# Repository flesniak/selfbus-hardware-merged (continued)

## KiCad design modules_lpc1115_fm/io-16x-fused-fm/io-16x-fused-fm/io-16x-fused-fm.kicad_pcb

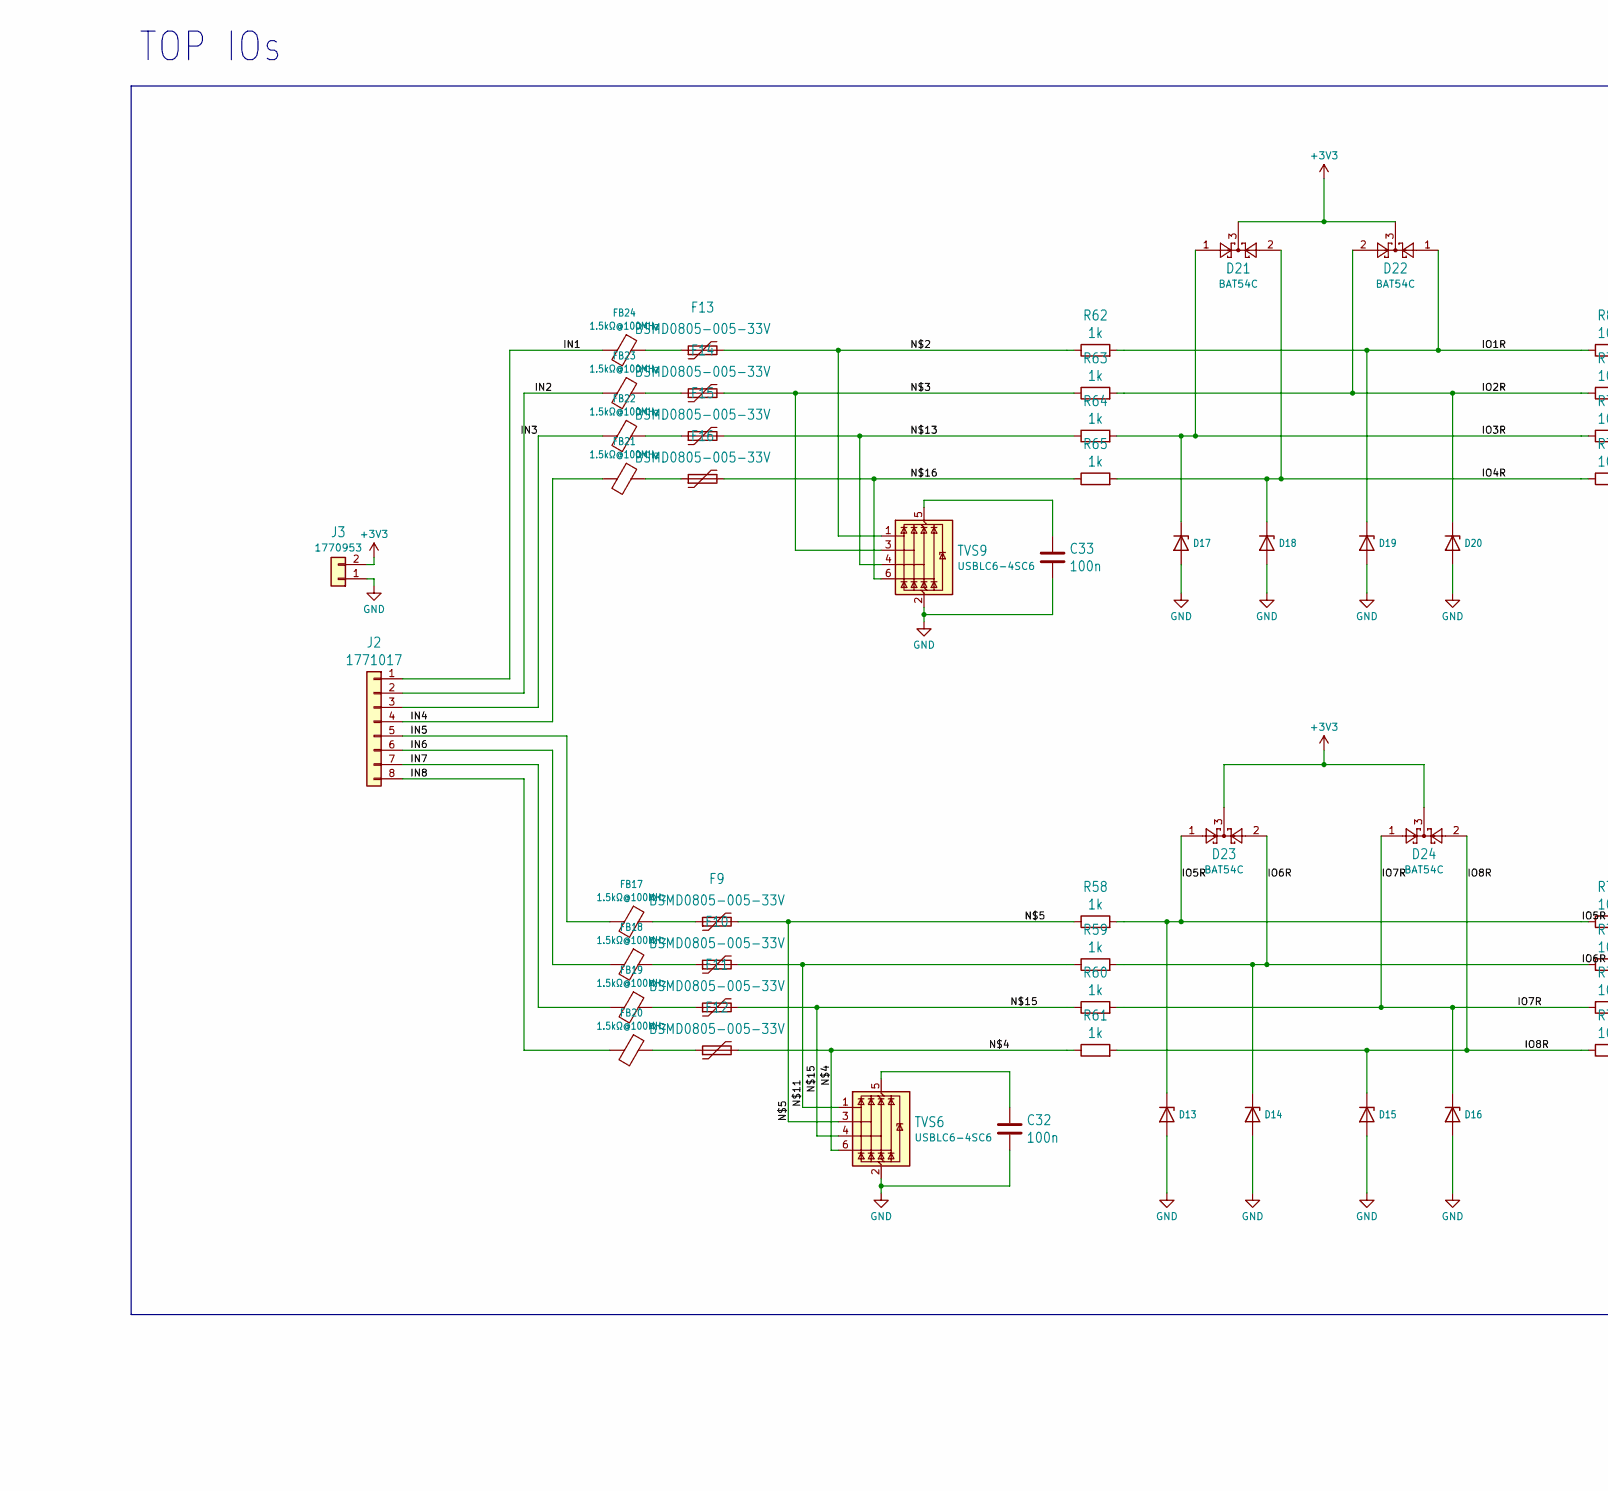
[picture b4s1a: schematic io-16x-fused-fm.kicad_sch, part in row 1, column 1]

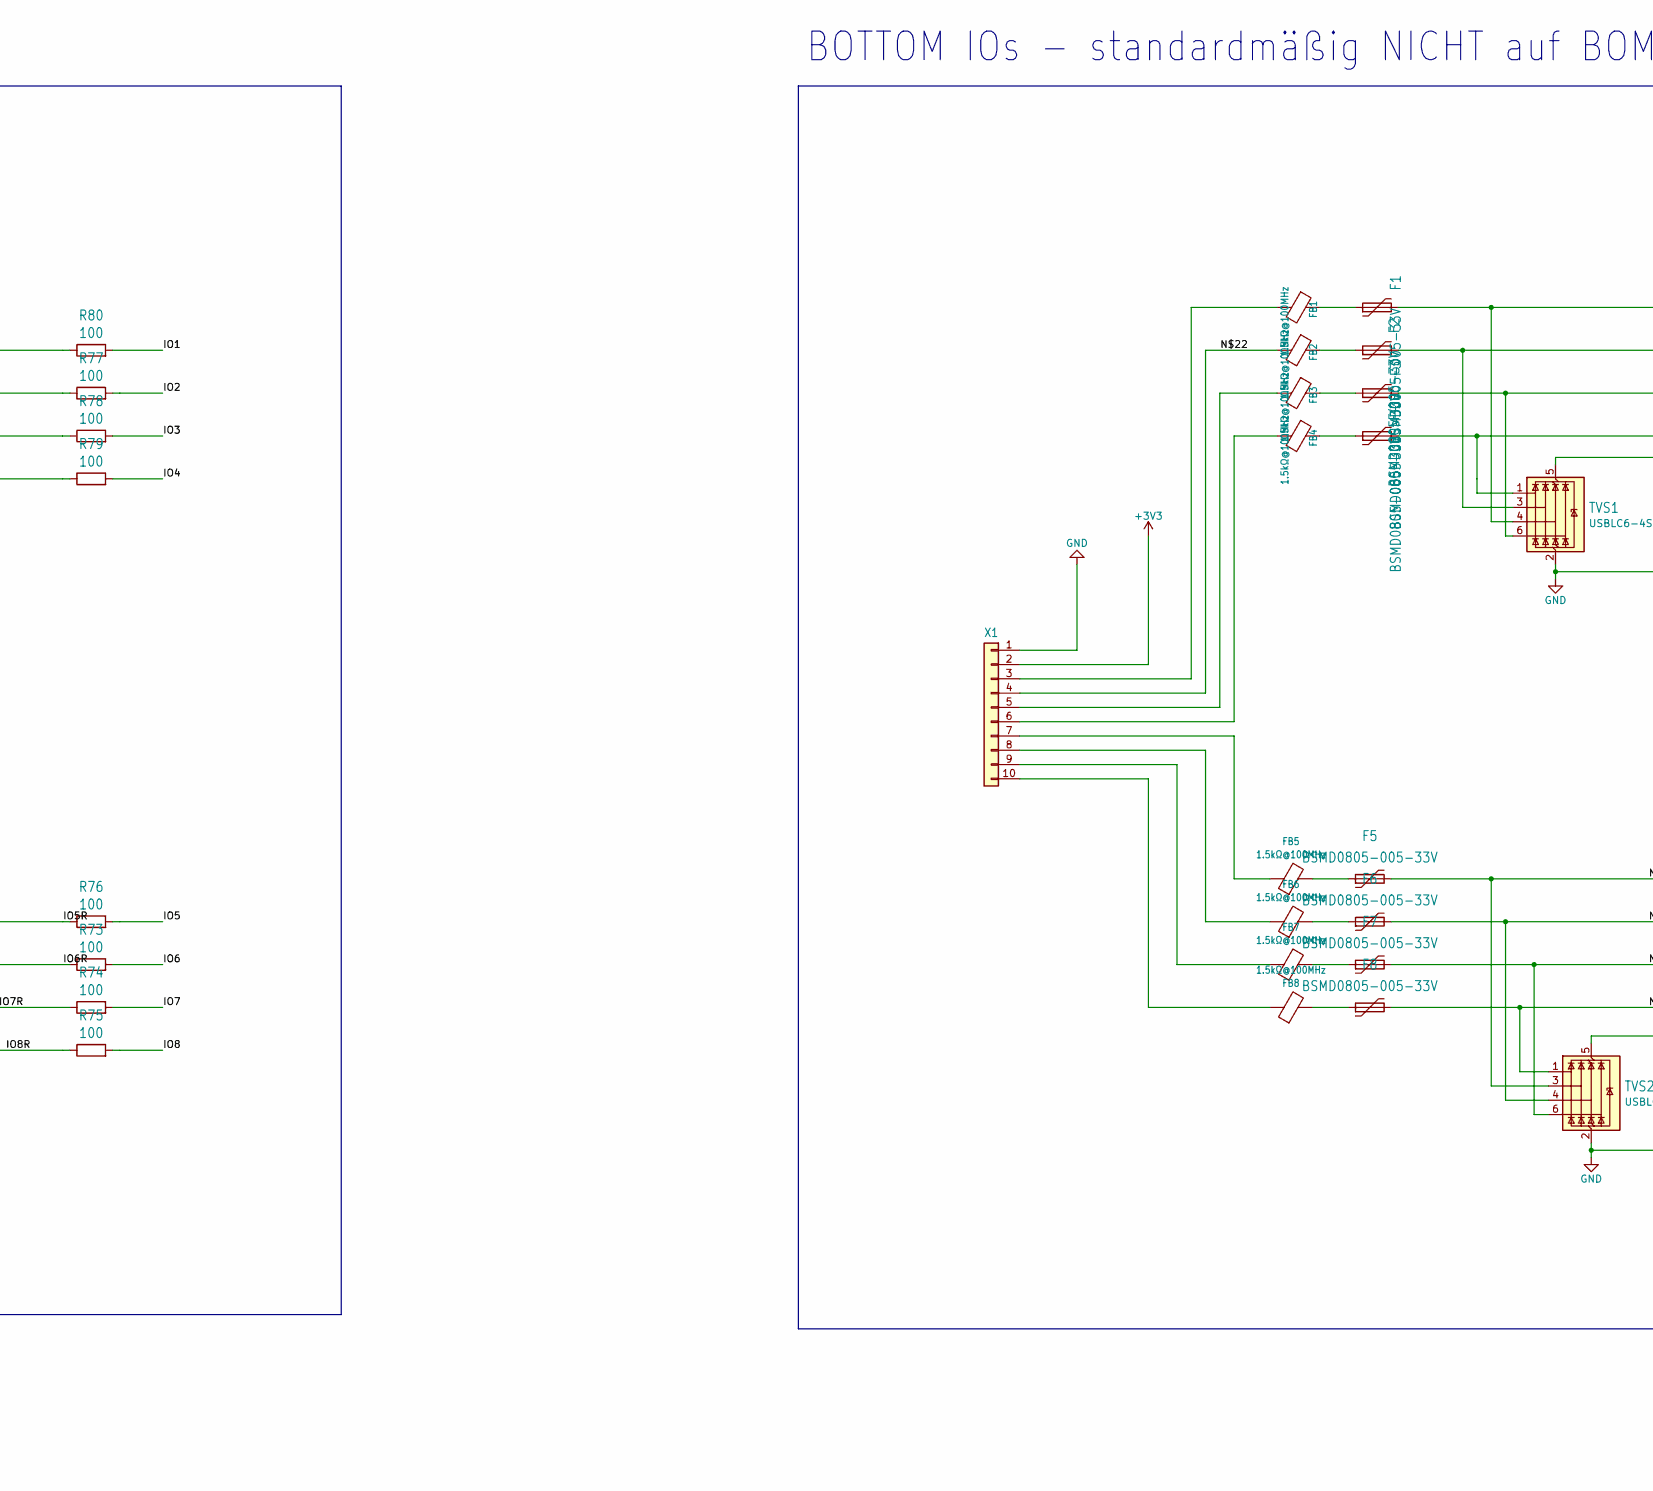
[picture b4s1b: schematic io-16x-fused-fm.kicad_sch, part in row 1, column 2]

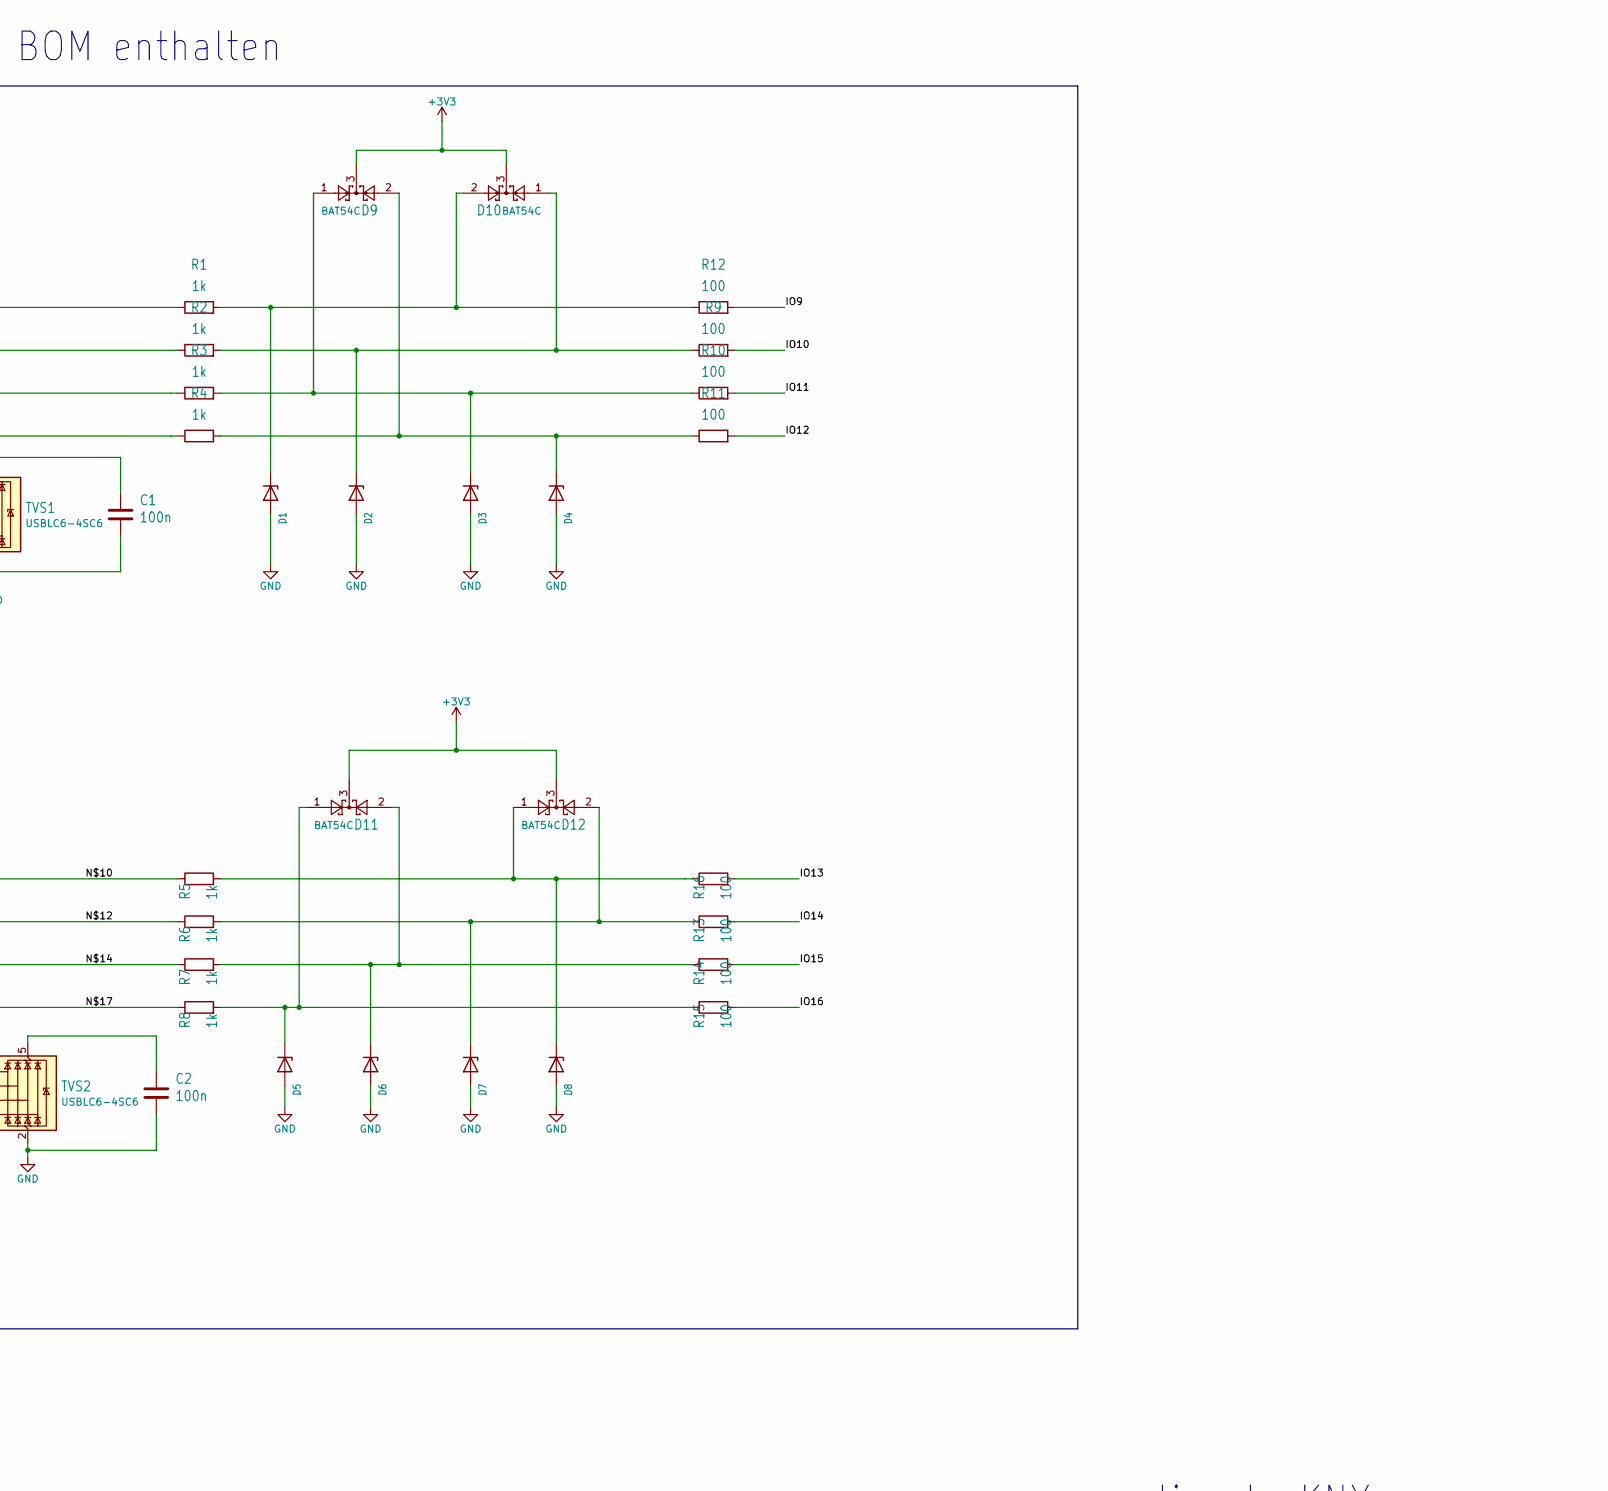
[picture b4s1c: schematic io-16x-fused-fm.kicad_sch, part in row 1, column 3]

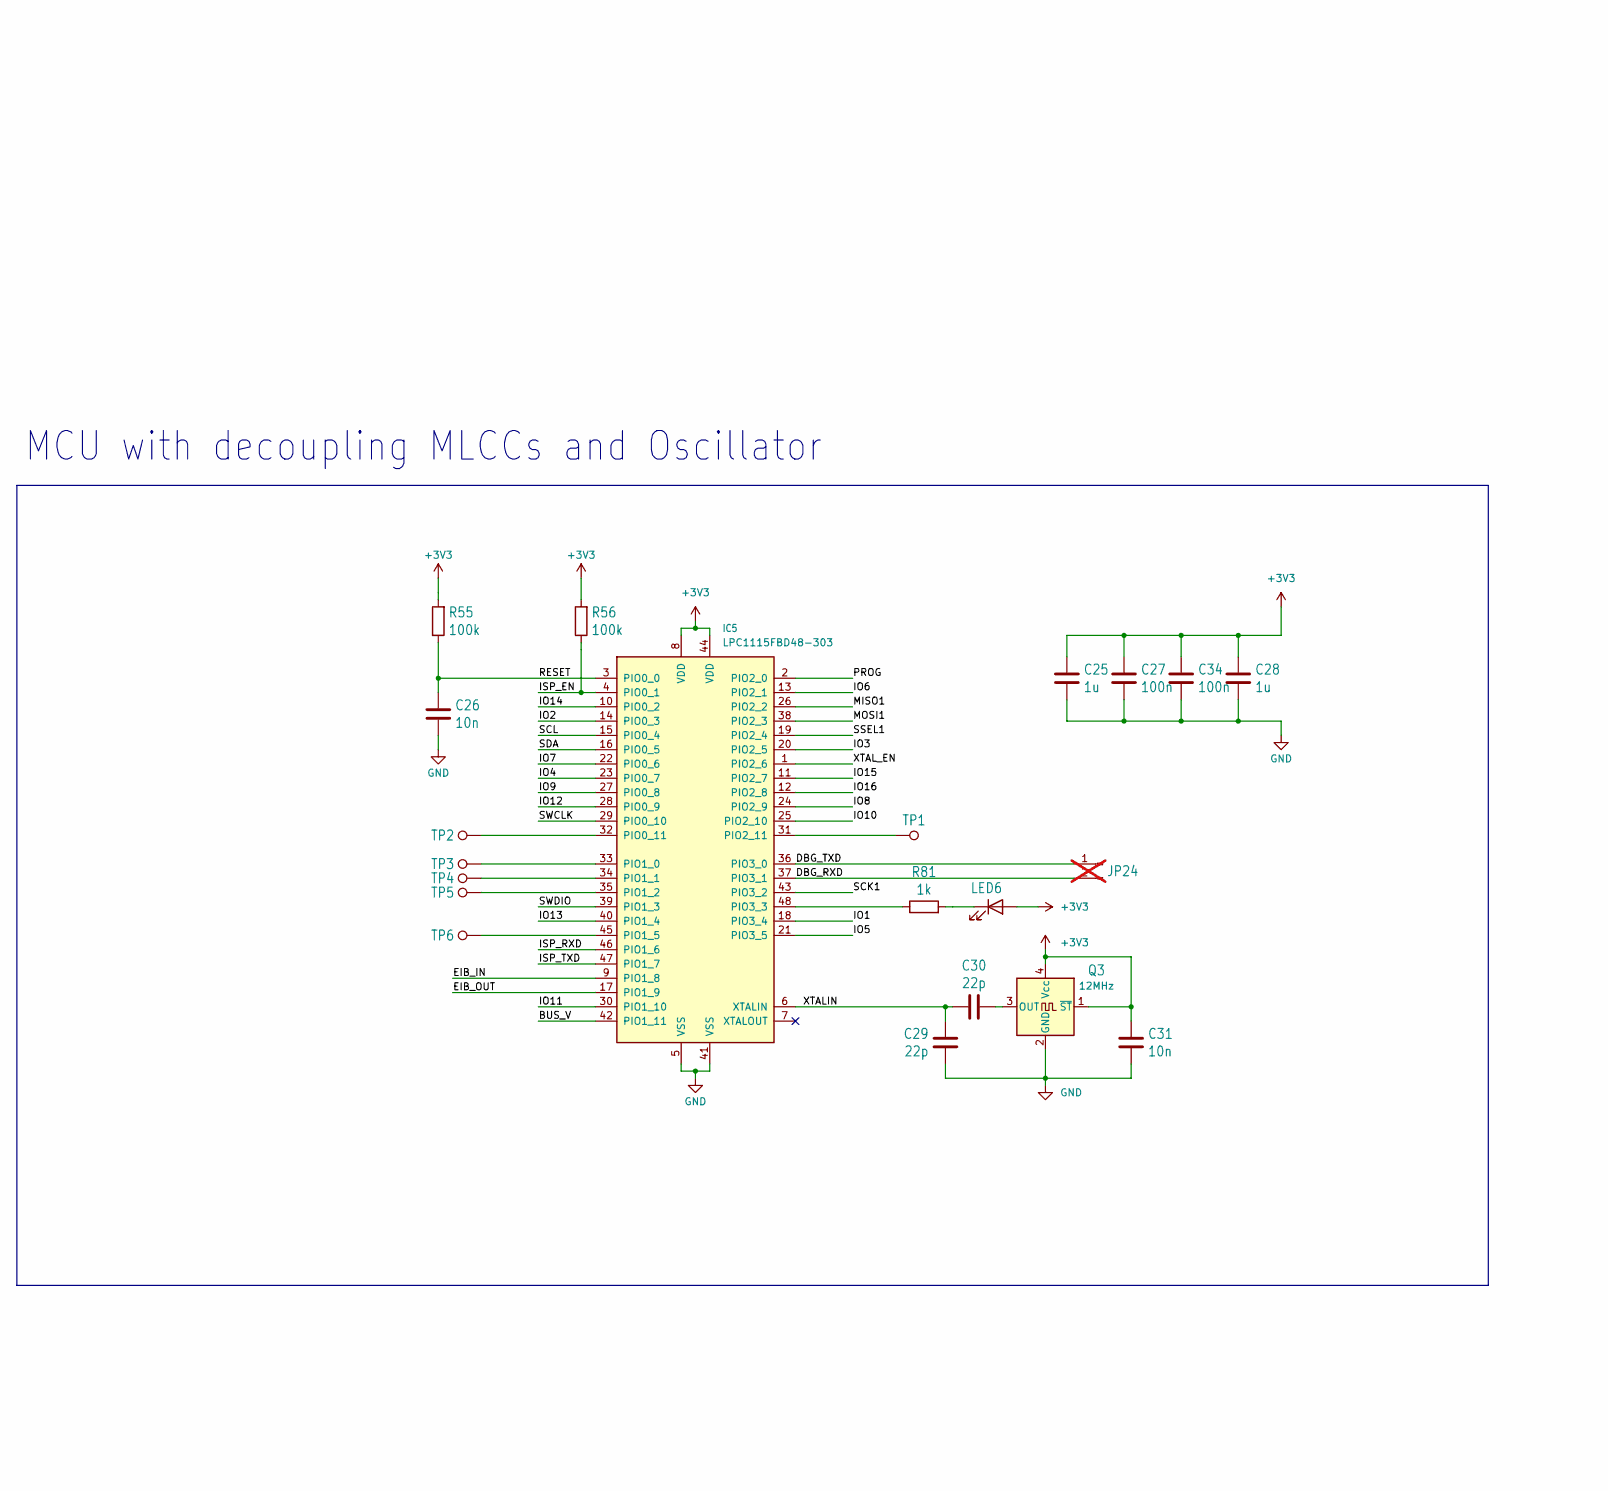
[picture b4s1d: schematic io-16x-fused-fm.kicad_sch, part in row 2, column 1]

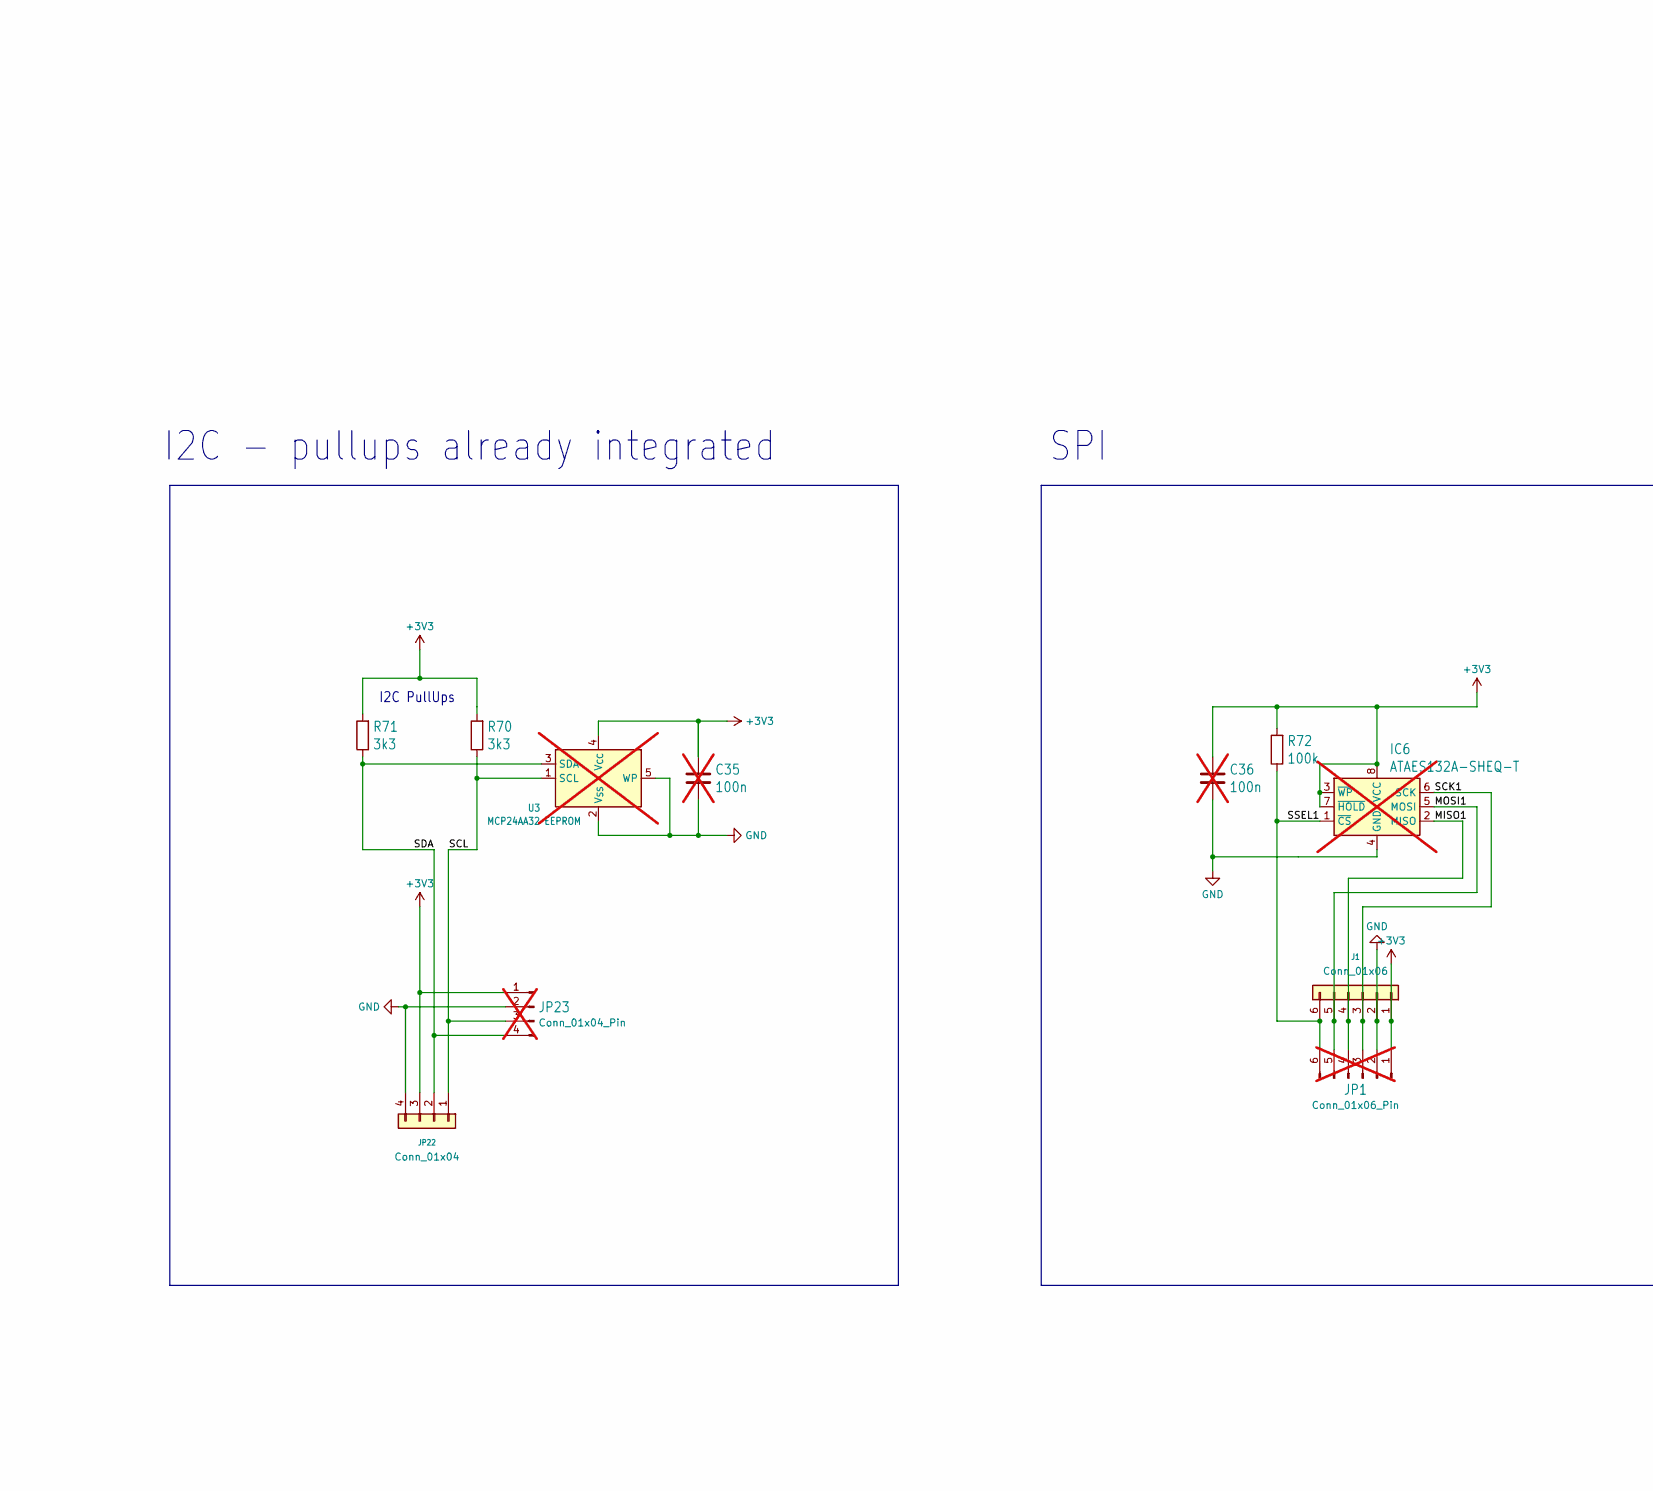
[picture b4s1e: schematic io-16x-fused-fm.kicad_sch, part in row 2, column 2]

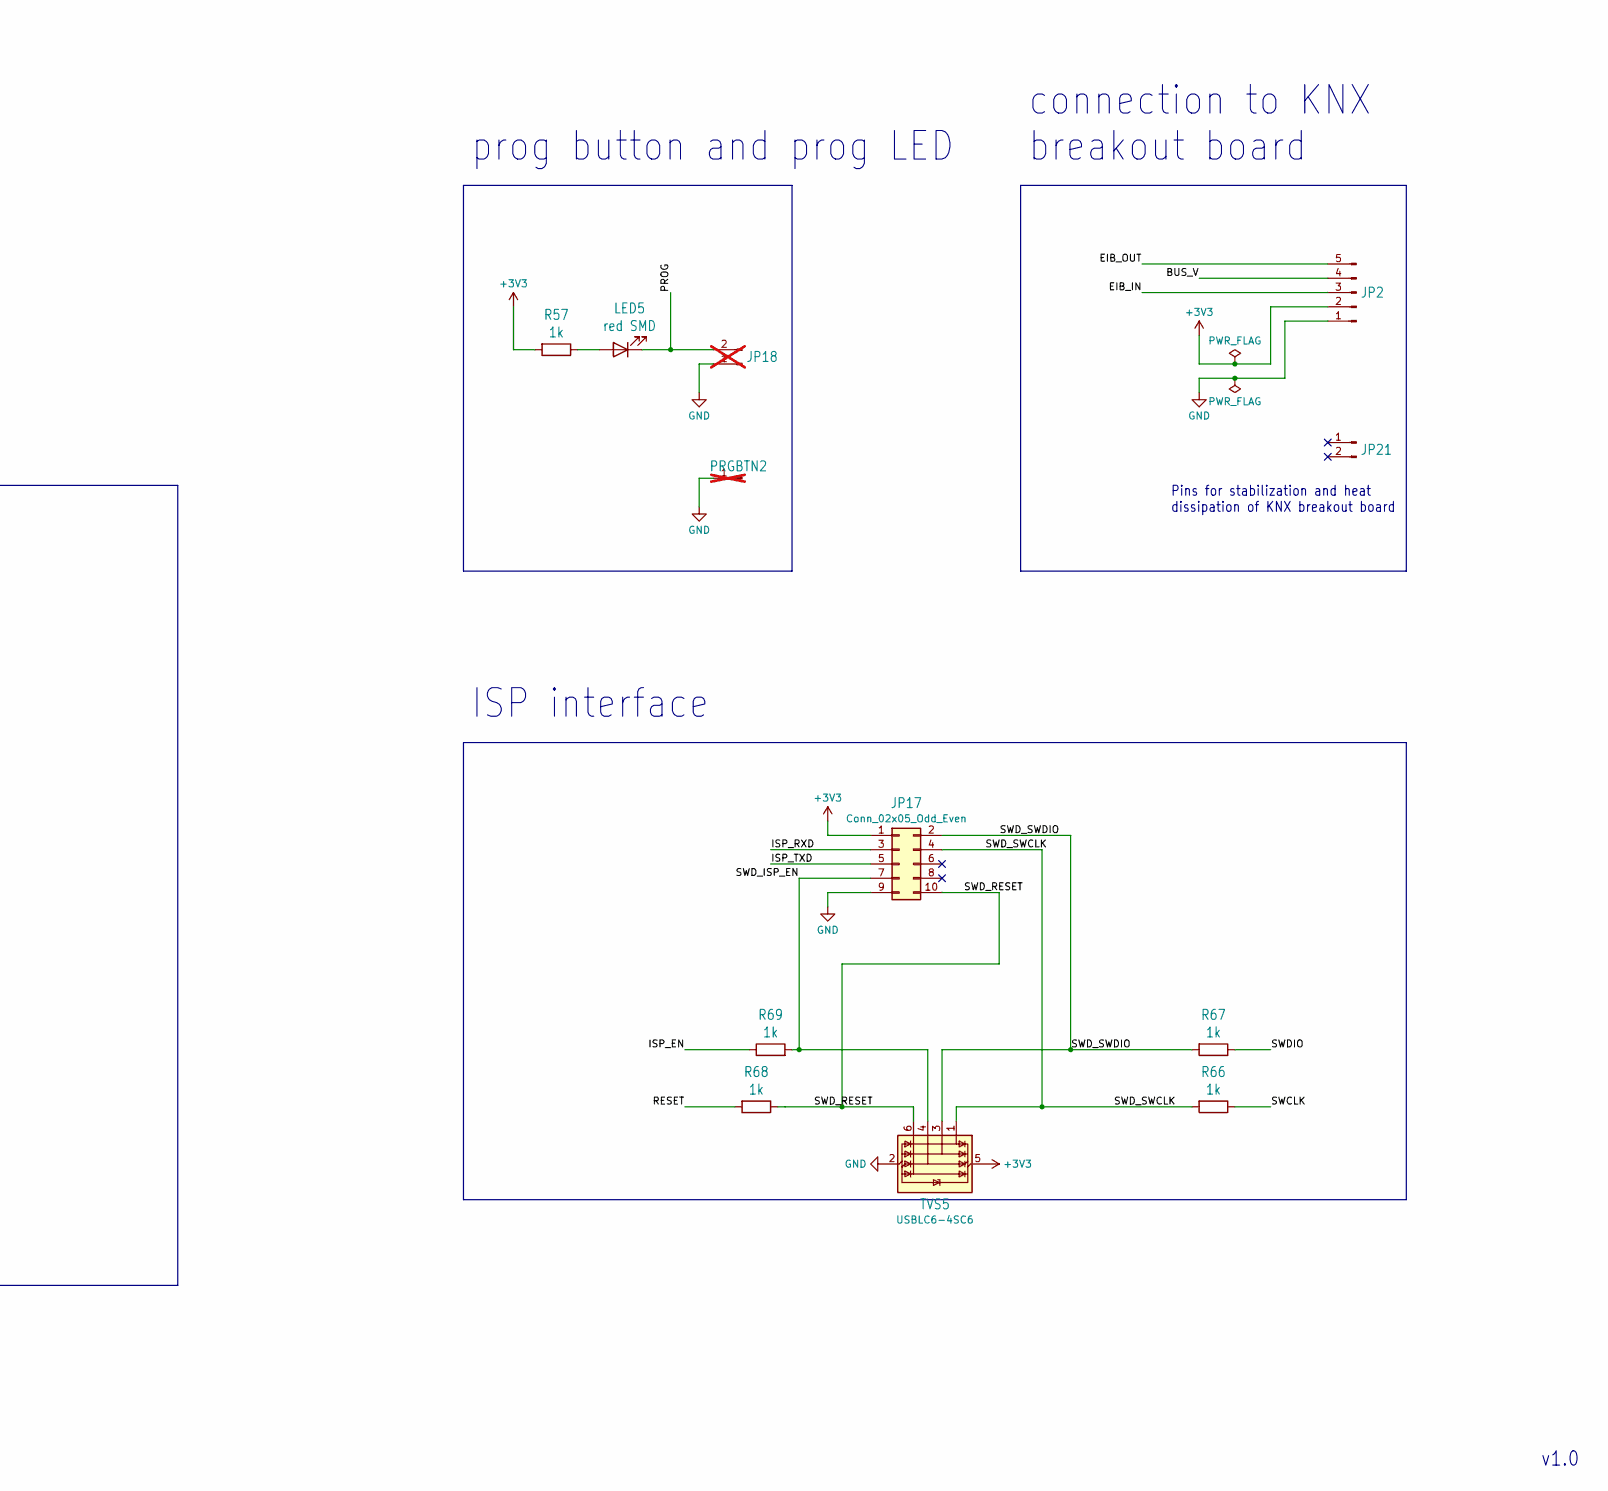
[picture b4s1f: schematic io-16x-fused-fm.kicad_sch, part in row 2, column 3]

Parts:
C1, C2, C27, C32, C33, C34: 100n; C_0805_2012Metric
C25, C28: 1u; C_0805_2012Metric
C26, C31: 10n; C_0805_2012Metric
C29, C30: 22p; C_0805_2012Metric
C35, C36: 100n; C_0805_2012Metric; not fitted
D1, D2, D3, D4, D5, D6, D7, D8, D13, D14, D15, D16, D17, D18, D19, D20: DDZ9684; D_SOD-123
D9, D10, D11, D12, D21, D22, D23, D24: BAT54C; SOT-23
F1, F2, F3, F4, F5, F6, F7, F8, F9, F10, F11, F12, F13, F14, F15, F16: BSMD0805-005-33V; Fuse_0805_2012Metric
FB1, FB2, FB3, FB4, FB5, FB6, FB7, FB8, FB17, FB18, FB19, FB20, FB21, FB22, FB23, FB24: 1.5kΩ@100MHz; L_0805_2012Metric
IC5: LPC1115FBD48-303; LQFP-48_7x7mm_P0.5mm
IC6: ATAES132A-SHEQ-T; SOIC-8_3.9x4.9mm_P1.27mm; not fitted
J1: Conn_01x06; JST_PH_B6B-PH-K_1x06_P2.00mm_Vertical
J2: 1771017; TerminalBlock_Phoenix_PTSM-0,5-8-2.5-V-THR_1x08_P2.50mm_Ver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
J3: 1770953; TerminalBlock_Phoenix_PTSM-0,5-2-2.5-V-THR_1x02_P2.50mm_Ver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
JP1: Conn_01x06_Pin; PinHeader_1x06_P2.54mm_Vertical_no_silkscreen; not fitted
JP2: PINHD-1X5; PinHeader_1x05_P2.54mm_Vertical
JP17: Conn_02x05_Odd_Even; PinHeader_2x05_P2.00mm_Vertical
JP18, JP24: PINHD-1X2; PinHeader_1x02_P2.54mm_Vertical; not fitted
JP21: PINHD-1X2; PinHeader_1x02_P2.54mm_Vertical
JP22: Conn_01x04; JST_PH_B4B-PH-K_1x04_P2.00mm_Vertical
JP23: Conn_01x04_Pin; PinHeader_1x04_P2.54mm_Vertical_no_silkscreen; not fitted
LED5: red SMD; LED_0805_2012Metric
LED6: LEDCHIPLED_0805; LED_0805_2012Metric
PRGBTN2: PINHD-1X1; PinHeader_1x01_P2.54mm_Vertical; not fitted
Q3: 12MHz; Oscillator_SMD_SeikoEpson_SG210-4Pin_2.5x2.0mm
R1, R2, R3, R4, R5, R6, R7, R8, R57, R58, R59, R60, R61, R62, R63, R64, R65, R66, R67, R68, R69, R81: 1k; R_0805_2012Metric
R9, R10, R11, R12, R13, R14, R15, R16, R73, R74, R75, R76, R77, R78, R79, R80: 100; R_0805_2012Metric
R55, R56, R72: 100k; R_0805_2012Metric
R70, R71: 3k3; R_0805_2012Metric
TP1, TP2, TP3, TP4, TP5, TP6: TPSQTP08R; TestPoint_Pad_D1.0mm
TVS1, TVS2, TVS5, TVS6, TVS9: USBLC6-4SC6; SOT-23-6
U3: MCP24AA32 EEPROM; SOT-23-5; not fitted
X1: MICROMATCH-10SMD; TE_Connectivity_MICRO-MATCH_SMD_FTE_1-188275-0_2x05_P1.27mm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

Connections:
+3V3: C25.2, C27.2, C28.2, C31.2, C34.2, C35.1, C36.1, D9.3, D10.3, D11.3, D12.3, D21.3, D22.3, D23.3, D24.3, IC5.8 (VDD), IC5.44 (VDD), IC6.3 (~WP), IC6.7 (~HOLD), IC6.8 (VCC), J1.1, J3.2, JP1.1, JP2.2, JP17.1, JP22.3, JP23.1, LED6.2 (A), Q3.1 (~ST), Q3.4 (Vcc), R55.2, R56.2, R57.2, R70.2, R71.2, R72.2, TVS5.5 (VBUS), U3.4 (V_{CC}), X1.2
/BUS_V: IC5.42 (PIO1_11), JP2.4
/DBG_RXD: IC5.37 (PIO3_1), JP24.2
/DBG_TXD: IC5.36 (PIO3_0), JP24.1
/EIB_IN: IC5.9 (PIO1_8), JP2.3
/EIB_OUT: IC5.17 (PIO1_9), JP2.5
/IN1: FB24.2, J2.1
/IN2: FB23.2, J2.2
/IN3: FB22.2, J2.3
/IN4: FB21.2, J2.4
/IN5: FB17.2, J2.5
/IN6: FB18.2, J2.6
/IN7: FB19.2, J2.7
/IN8: FB20.2, J2.8
/IO1: IC5.18 (PIO3_4), R80.2
/IO1R: D19.1 (K), D22.1, R62.2, R80.1
/IO2: IC5.14 (PIO0_3), R77.2
/IO2R: D20.1 (K), D22.2, R63.2, R77.1
/IO3: IC5.20 (PIO2_5), R78.2
/IO3R: D17.1 (K), D21.1, R64.2, R78.1
/IO4: IC5.23 (PIO0_7), R79.2
/IO4R: D18.1 (K), D21.2, R65.2, R79.1
/IO5: IC5.21 (PIO3_5), R76.2
/IO5R: D13.1 (K), D23.1, R58.2, R76.1
/IO6: IC5.13 (PIO2_1), R73.2
/IO6R: D14.1 (K), D23.2, R59.2, R73.1
/IO7: IC5.22 (PIO0_6), R74.2
/IO7R: D16.1 (K), D24.1, R60.2, R74.1
/IO8: IC5.24 (PIO2_9), R75.2
/IO8R: D15.1 (K), D24.2, R61.2, R75.1
/IO9: IC5.27 (PIO0_8), R12.2
/IO10: IC5.25 (PIO2_10), R9.2
/IO11: IC5.30 (PIO1_10), R10.2
/IO12: IC5.28 (PIO0_9), R11.2
/IO13: IC5.40 (PIO1_4), R16.2
/IO14: IC5.10 (PIO0_2), R13.2
/IO15: IC5.11 (PIO2_7), R14.2
/IO16: IC5.12 (PIO2_8), R15.2
/ISP_EN: IC5.4 (PIO0_1), R56.1, R69.1
/ISP_RXD: IC5.46 (PIO1_6), JP17.3
/ISP_TXD: IC5.47 (PIO1_7), JP17.5
/MISO1: IC5.26 (PIO2_2), IC6.2 (MISO), J1.4, JP1.4
/MOSI1: IC5.38 (PIO2_3), IC6.5 (MOSI), J1.5, JP1.5
/N$2: F13.2, R62.1, TVS9.1 (I/O1)
/N$3: F14.2, R63.1, TVS9.3 (I/O2)
/N$4: F12.2, R61.1, TVS6.6 (I/O4)
/N$5: F9.2, R58.1, TVS6.3 (I/O2)
/N$10: F5.2, R5.1, TVS2.3 (I/O2)
/N$11: F10.2, R59.1, TVS6.1 (I/O1)
/N$12: F6.2, R6.1, TVS2.4 (I/O3)
/N$13: F15.2, R64.1, TVS9.4 (I/O3)
/N$14: F7.2, R7.1, TVS2.6 (I/O4)
/N$15: F11.2, R60.1, TVS6.4 (I/O3)
/N$16: F16.2, R65.1, TVS9.6 (I/O4)
/N$17: F8.2, R8.1, TVS2.1 (I/O1)
/N$22: FB2.2, X1.4
/PROG: IC5.2 (PIO2_0), JP18.2, LED5.1 (K)
/RESET: C26.2, IC5.3 (PIO0_0), R55.1, R68.2
/SCK1: IC5.43 (PIO3_2), IC6.6 (SCK), J1.3, JP1.3
/SCL: IC5.15 (PIO0_4), JP22.1, JP23.3, R70.1, U3.1 (SCL)
/SDA: IC5.16 (PIO0_5), JP22.2, JP23.4, R71.1, U3.3 (SDA)
/SSEL1: IC5.19 (PIO2_4), IC6.1 (~CS), J1.6, JP1.6, R72.1
/SWCLK: IC5.29 (PIO0_10), R66.1
/SWDIO: IC5.39 (PIO1_3), R67.1
/SWD_ISP_EN: JP17.7, R69.2, TVS5.4 (I/O3)
/SWD_RESET: JP17.10, R68.1, TVS5.6 (I/O4)
/SWD_SWCLK: JP17.4, R66.2, TVS5.1 (I/O1)
/SWD_SWDIO: JP17.2, R67.2, TVS5.3 (I/O2)
/XTALIN: C29.2, C30.1, IC5.6 (XTALIN)
/XTAL_EN: IC5.1 (PIO2_6)
GND: C1.1, C2.1, C25.1, C26.1, C27.1, C28.1, C29.1, C31.1, C32.1, C33.1, C34.1, C35.2, C36.2, D1.2 (A), D2.2 (A), D3.2 (A), D4.2 (A), D5.2 (A), D6.2 (A), D7.2 (A), D8.2 (A), D13.2 (A), D14.2 (A), D15.2 (A), D16.2 (A), D17.2 (A), D18.2 (A), D19.2 (A), D20.2 (A), IC5.5 (VSS), IC5.41 (VSS), IC6.4 (GND), J1.2, J3.1, JP1.2, JP2.1, JP17.9, JP18.1, JP22.4, JP23.2, PRGBTN2.1, Q3.2 (GND), TVS1.2 (GND), TVS2.2 (GND), TVS5.2 (GND), TVS6.2 (GND), TVS9.2 (GND), U3.2 (V_{SS}), U3.5 (WP), X1.1
unnamed: D1.1 (K), D10.2, R1.2, R12.1
unnamed: D2.1 (K), D10.1, R2.2, R9.1
unnamed: D3.1 (K), D9.1, R3.2, R10.1
unnamed: D4.1 (K), D9.2, R4.2, R11.1
unnamed: D5.1 (K), D11.1, R8.2, R15.1
unnamed: D6.1 (K), D11.2, R7.2, R14.1
unnamed: D7.1 (K), D12.2, R6.2, R13.1
unnamed: D8.1 (K), D12.1, R5.2, R16.1
unnamed: F1.1, FB1.1
unnamed: F2.1, FB2.1
unnamed: F3.1, FB3.1
unnamed: F4.1, FB4.1
unnamed: F5.1, FB5.2
unnamed: F6.1, FB6.2
unnamed: F7.1, FB7.2
unnamed: F8.1, FB8.2
unnamed: F9.1, FB17.1
unnamed: F10.1, FB18.1
unnamed: F11.1, FB19.1
unnamed: F12.1, FB20.1
unnamed: F13.1, FB24.1
unnamed: F14.1, FB23.1
unnamed: F15.1, FB22.1
unnamed: F16.1, FB21.1
unnamed: IC5.32 (PIO0_11), TP2.1
unnamed: IC5.33 (PIO1_0), TP3.1
unnamed: IC5.34 (PIO1_1), TP4.1
unnamed: IC5.35 (PIO1_2), TP5.1
unnamed: IC5.45 (PIO1_5), TP6.1
unnamed: IC5.31 (PIO2_11), TP1.1
unnamed: IC5.48 (PIO3_3), R81.1
unnamed: LED5.2 (A), R57.1
unnamed: LED6.1 (K), R81.2
unnamed: C30.2, Q3.3 (OUT)
unnamed: F4.2, R4.1, TVS1.1 (I/O1)
unnamed: F2.2, R2.1, TVS1.3 (I/O2)
unnamed: F1.2, R1.1, TVS1.4 (I/O3)
unnamed: F3.2, R3.1, TVS1.6 (I/O4)
unnamed: C1.2, TVS1.5 (VBUS)
unnamed: C2.2, TVS2.5 (VBUS)
unnamed: C32.2, TVS6.5 (VBUS)
unnamed: C33.2, TVS9.5 (VBUS)
unnamed: FB1.2, X1.3
unnamed: FB3.2, X1.5
unnamed: FB4.2, X1.6
unnamed: FB5.1, X1.7
unnamed: FB6.1, X1.8
unnamed: FB7.1, X1.9
unnamed: FB8.1, X1.10

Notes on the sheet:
Pins for stabilization and heat dissipation of KNX breakout board
SPI
I2C PullUps
v1.0
BOTTOM IOs - standardmäßig NICHT auf BOM enthalten
prog button and prog LED
ISP interface
I2C - pullups already integrated
connection to KNX breakout board
MCU with decoupling MLCCs and Oscillator
TOP IOs

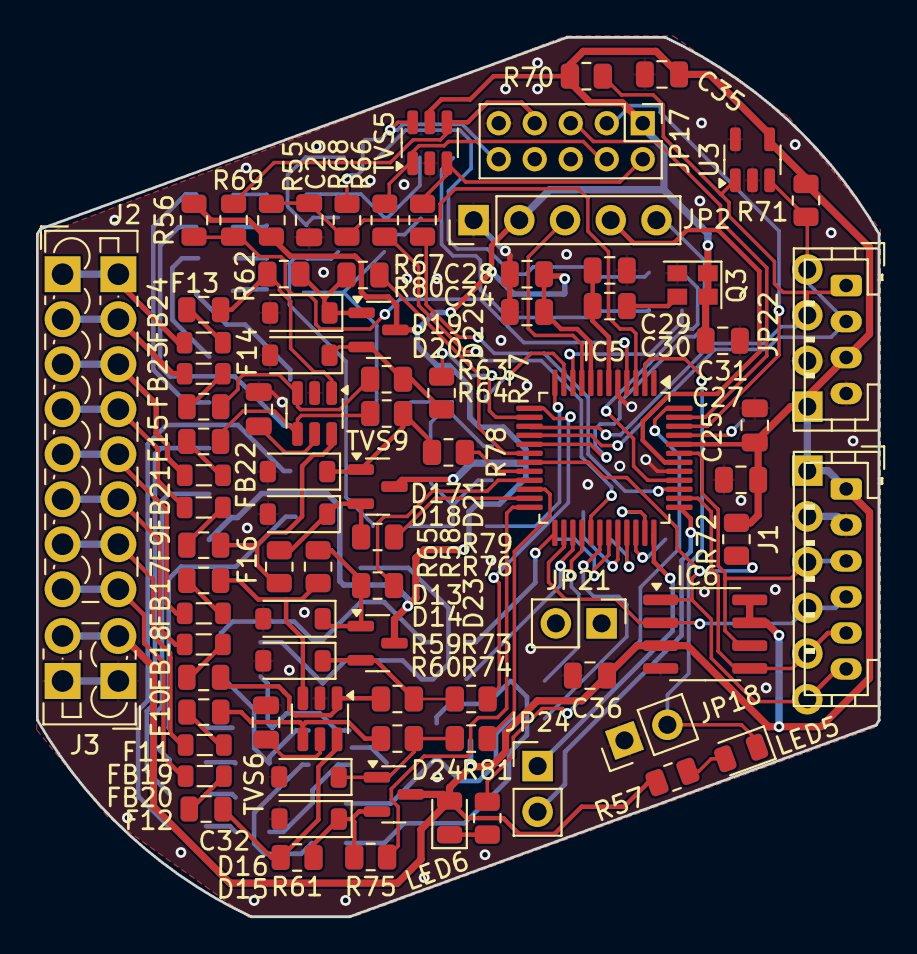
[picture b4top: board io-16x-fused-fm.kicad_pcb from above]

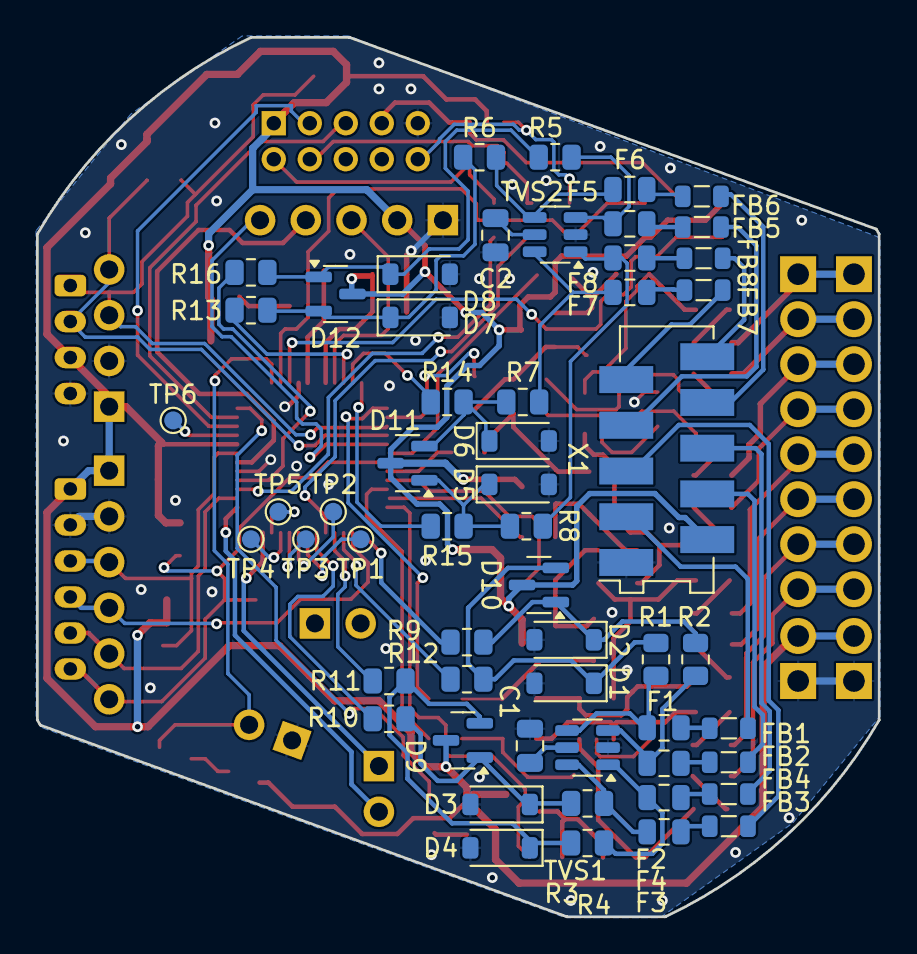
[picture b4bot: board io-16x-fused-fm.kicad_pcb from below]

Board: 2 copper layers, 46.8 x 48.9 mm, 142 parts (55 on the bottom side), 119 nets.
